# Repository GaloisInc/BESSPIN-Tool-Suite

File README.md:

```
This material is based upon work supported by the Defense Advanced
Research Project Agency (DARPA) under Contract No. HR0011-18-C-0013. 
Any opinions, findings, conclusions or recommendations expressed in
this material are those of the author(s) and do not necessarily
reflect the views of DARPA.

Distribution Statement "A" (Approved for Public Release, Distribution
Unlimited)
```

# BESSPIN-Tool-Suite #

The core tool of the BESSPIN Framework.

**Disclaimer:** *This is prototype beta software*, with support
provided to SSITH TA-1 teams.  It does not currently implement all
planned features, and contains bugs both known and unknown.  If
you encounter a problem or would like to request improvements, please
contact Galois through documented support channels.

## Table of Contents ##

- [Overview](#overview)
- [Software Requirements and Setup](#software-requirements-and-setup)
- [Usage](#usage)
- [Submodules](#submodules)
- [Developer Starter Kit](#developer-starter-kit)

___

## Overview ##

The tool performs a few different *tasks* that all revolve around the same *function*. The motivation behind the core functionality, i.e. the *function*, is to run a *program* on a target-under-test (TUT) in a robust and reproducible manner, where the TUT can be of multiple different OSes running on several different processor architectures running on multiple different backends.

In particular, the different *tasks* are called *modes*, and their different tool flows are described in detail in [modes.md](./docs/base/modes.md). The bug bounty modes have more details in [this directory](./docs/bugBounty2020/), the security evaluation mode is described in detail [here](./docs/cwesEvaluation/), and the cyberphysical demonstrator's documentation can be found [here](./docs/cyberPhys).

The different OSes are detailed in [OSes.md](./docs/base/OSes.md), while the different processors are mentioned [here](./docs/base/configuration.md), and the different backends are explained in [targets.md](./docs/base/targets.md).

---

## Software Requirements and Setup

To clone the repo and start `the nix-shell`, please use:

```bash
git clone git@github.com:GaloisInc/BESSPIN-Tool-Suite.git
cd BESSPIN-Tool-Suite
./utils/init_submodules.sh
nix-shell
```

- The `nix-shell` is the interactive shell for the Nix package manager. Please refer to [nix.md](./docs/base/nix.md) for more setup details. Please note that Nix, per version 2.3.10, is only supported on Linux (i686, x86_64, aarch64) and macOS (x86_64). [Ticket #1051 is about running the tool out-of-nix.]
- Each backend (target) has different system and setup requirements, these can be found in [targets.md](./docs/base/targets.md).
- Sudo privileges: Some parts of the tool might need sudo privileges, especially for network setup and hardware drivers access. If you do not wish to be attentive to the tool, you may just allow any sudo member to execute a group of commands without password by adding the following to the sudoers file:
```bash
    %sudo ALL=NOPASSWD: /path/to/command [flags], /path/to/another/command [flags]
```
Also, a more radical approach would be to remove all password requirements for a certain user, `${USER}`. The following can be thus added to the sudoers file:
```
${USER} ALL=(ALL) NOPASSWD:ALL
```

Alternatively, there is a docker container that has the Nix store populated, and is ready to go. The resources needed to build the docker container are currently in [the docker directory](https://github.com/GaloisInc/BESSPIN-Environment/tree/master/docker/). The docker image is `galoisinc/besspin:tool-suite`, and requires Galois artifactory access to fetch. The recommended command to start the image is:
```bash
    sudo docker run -it --privileged=true --network host -v /path/to/BESSPIN-Tool-Suite:/home/besspinuser/BESSPIN-Tool-Suite galoisinc/besspin:tool-suite
```

---

## Usage ##

To run the tool, use the following:
```
usage: besspin.py [-h] [-c CONFIGFILE | -cjson CONFIGFILESERIALIZED]
               [-w WORKINGDIRECTORY] [-l LOGFILE] [-d]
               [-ep {devHost,ciOnPrem,ciAWS,awsProd,awsDev}] [-job JOBID]

BESSPIN (Balancing Evaluation of System Security Properties with Industrial Needs)

optional arguments:
  -h, --help            show this help message and exit
  -c CONFIGFILE, --configFile CONFIGFILE
                        Overwrites the default config file: ./config.ini
  -cjson CONFIGFILESERIALIZED, --configFileSerialized CONFIGFILESERIALIZED
                        Overwrites and augments the default production
                        settings
  -w WORKINGDIRECTORY, --workingDirectory WORKINGDIRECTORY
                        Overwrites the default working directory: ./workDir/
  -l LOGFILE, --logFile LOGFILE
                        Overwrites the default logFile: ./${workDir}/besspin.log
  -d, --debug           Enable debugging mode.
  -ep {devHost,ciOnPrem,ciAWS,awsProd,awsDev}, --entrypoint {devHost,ciOnPrem,ciAWS,awsProd,awsDev}
                        The entrypoint
  -job JOBID, --jobId JOBID
                        The job ID in production mode.
```

Configuration is explained in detail in [configuration.md](./docs/base/configuration.md). Although `-cjson` is an alternative option, it is strongly recommended to use an INI file as the document describes. The serialized option is specific to the production mode in bug bounty, and is intended to be used automatically by a cloud hook script on a host instantiated by the bug bounty website; more details can be found in [the bug bounty documentation](./docs/bugBounty2020/).

If the tool is executed manually, there is no need to provide an entrypoint (will be assigned `devHost` by default), or a job ID. These are for when the tool is executed in batch test mode and CI.

The debug mode will dramatically increase the size of the log file (`./${workDir}/besspin.log` by default), so please use it only if needed.

---

## Submodules ##

The tool has the following submodules:
- [BESSPIN-Environment](./BESSPIN-Environment): The Nix shell source codes for the required packages and binaries. More details about Nix are in [nix.md](./docs/base/nix.md).
- [BESSPIN-Voter-Registration](./BESSPIN-Voter-Registration): As detailed [here](./docs/bugBounty2020/), a voting registration system was one of the applications in the attack surface for the Unix targets of the bug bounty. This submodule has documentation, build instructions, source codes, design files, etc.
- [BESSPIN-LFS](./BESSPIN-LFS): This is the Git LFS repo that contains many resources the tool needs for certain configurations, like OS binaries, FPGA bitstreams, AWS AFI IDs, application pre-built binaries, etc.
- [FreeRTOS](./FreeRTOS): The Galois fork of the classic FreeRTOS repo. This is used for building the FreeRTOS binaries since each CWE test and each application needs to be cross-built alongside the FreeRTOS kernel in a single binary. 

---

## Developer Starter Kit ##

- The target classes structure is briefly explained in [targets.md](./docs/base/targets.md). This should be the starting point to add a new OS or a new backend to the tool.
- There are many functions that are used throughout the tool and can help with integration. These functions are defined inside `besspin/base/utils/misc.py`. It would be useful to look at this file prior to any development work on this codebase. Especially `printAndLog`, `warnAndLog`, `errorAndLog`, `logAndExit`, `getSetting`, `ftOpenFile`, `make`.
- To add a configuration option, you have to update the json dictionary in `besspin/base/utils/configData.json`.
- To add/change a system setting, you have to update the json dictionary in `besspin/base/utils/setupEnv.json`.
- The directories structure is:
  - `apps`: Bug bounty specific.
  - `base`: The core functionality (ex. target)
  - `cwesEvaluation`: Security evaluation specific.
  - `cyberPhys`: Cyberphysical demonstrator functions.
  - `target`: The backend classes in addition to the start/launch/end functions.
- [modes.md](./docs/base/modes) has some low-level details about how the tool works in different modes. It's definitely a recommended read before development.

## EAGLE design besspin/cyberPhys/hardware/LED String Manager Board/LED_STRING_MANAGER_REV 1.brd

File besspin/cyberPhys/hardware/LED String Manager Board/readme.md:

# Introduction
The LED String Manager Board is a Fadecandy-based LED string manager solution which provides a tidy, robust power and data solution for strings of individually addressable 12 volt LEDs commonly referred to as Neopixels.

Up to eight strings of 63 LEDs can be driven using this board. A Fadecandy board and a USB relay are necessary.

Schematic and Board were created using Eagle 9.6.2 Premium. The following design artifacts are included in this repository:
- Schematic and Board Layout files
- Bill of Materials
- Gerber files

# 12 Volt Power
The board is powered with 12 volts through common 0.250 inch spade connectors. Wiring which can accommodate up to 7.5 amperes is recommended as well as a 7.5 ampere automotive standard blade fuse.

# LED String Interface
Each LED string _requires_ three circuits:
- 12 volts (Blue)
- Data (Red)
- Ground (Black)

There is a second, backup data line which is not used.

Each LED string is terminated in a JST P/N SMP-04V-BC connector as shown in the following image.

Any 100 mil spaced male header may be used for LED string connections at CN2 through CN9. The boards in the CyberPhysical demonstrator use Molex P/N 0901361204, which is a shrouded header with a key clip. Each four circuit harness used in the CyberPhysical demonstrator consists of the following:

- 1 x Molex P/N 0901560144 (housing)
- 4 x Molex P/N 0901192109 (crimp contacts, requires Molex Crimp Tool P/N 0638258100)
- Varied length of 4-circuit LED extension wire
- 1 x JST P/N SMR-04V-B (housing)
- 4 x JST P/N SYM-001T-P0.6(N) (crimp contacts)

Pin #1 of the Molex connector is 12 volts (Blue).

# Example Installation
The following image shows an LED String Manager Board installed in the CyberPhysical demonstrator with variable length LED string interface harnesses.

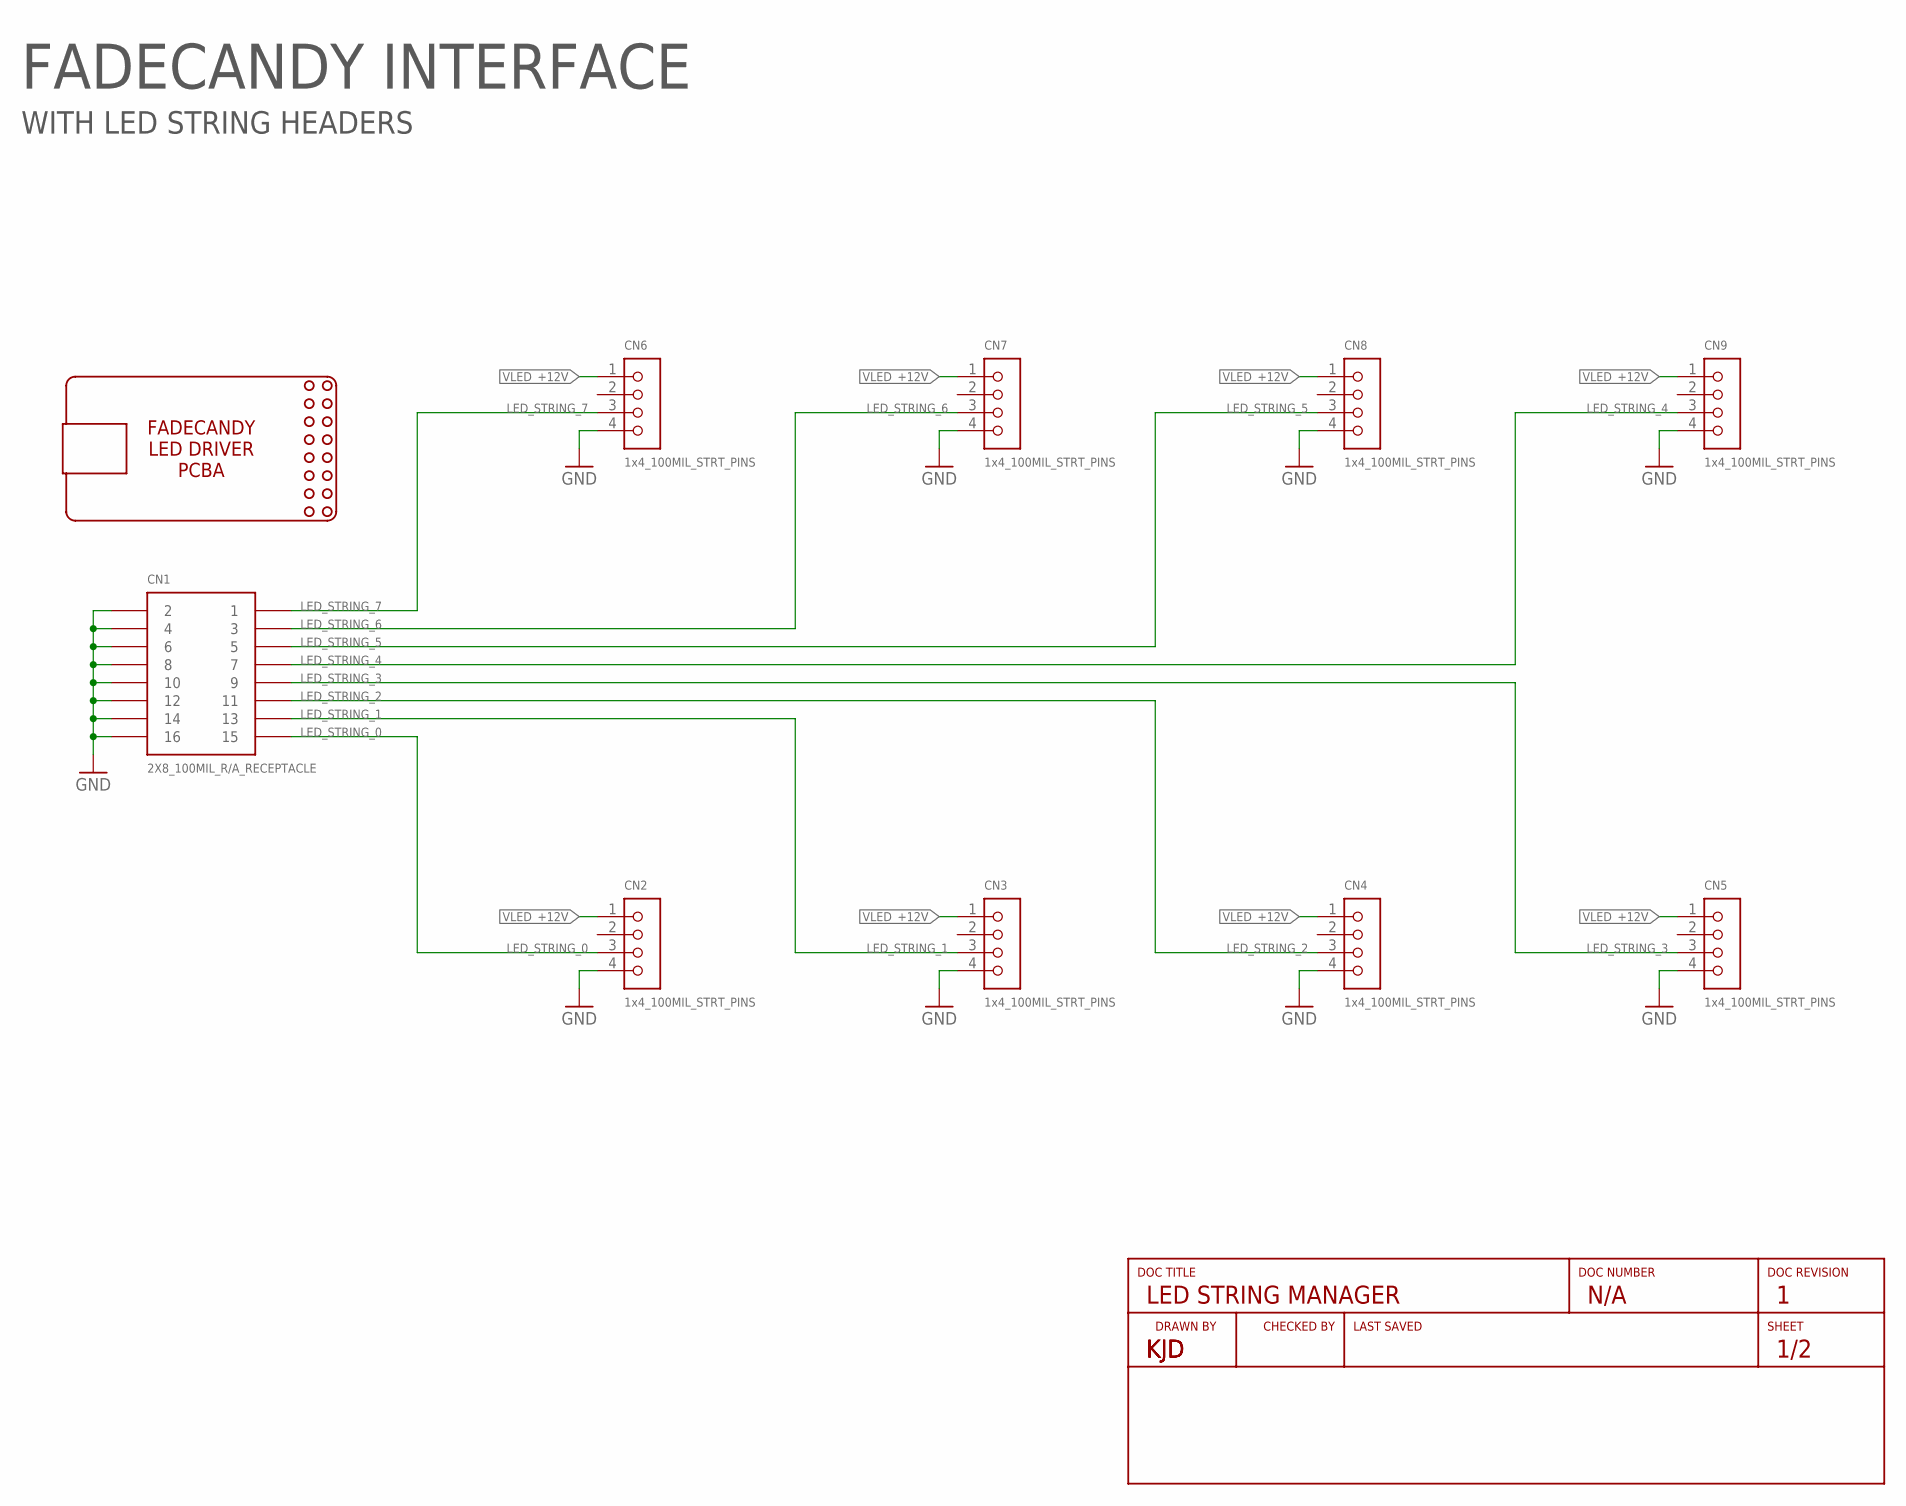
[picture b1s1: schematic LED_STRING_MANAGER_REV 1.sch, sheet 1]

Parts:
CN1: 2X8_100MIL_R/A_RECEPTACLE; 2X8_100MIL_R/A; MPN PPPC082LJBN-RC
CN2, CN3, CN4, CN5, CN6, CN7, CN8, CN9: 1x4_100MIL_STRT_PINS; 1X4_0901361204; MPN 0901361204
U$3: FADECANDY_PCB_FOOTPRINT

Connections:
GND: CN1.2, CN1.4, CN1.6, CN1.8, CN1.10, CN1.12, CN1.14, CN1.16, CN2.4, CN3.4, CN4.4, CN5.4, CN6.4, CN7.4, CN8.4, CN9.4; also elsewhere on the board
LED_STRING_0: CN1.15, CN2.3
LED_STRING_1: CN1.13, CN3.3
LED_STRING_2: CN1.11, CN4.3
LED_STRING_3: CN1.9, CN5.3
LED_STRING_4: CN1.7, CN9.3
LED_STRING_5: CN1.5, CN8.3
LED_STRING_6: CN1.3, CN7.3
LED_STRING_7: CN1.1, CN6.3
VLED_+12V: CN2.1, CN3.1, CN4.1, CN5.1, CN6.1, CN7.1, CN8.1, CN9.1; also elsewhere on the board

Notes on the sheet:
FADECANDY INTERFACE
WITH LED STRING HEADERS
KJD

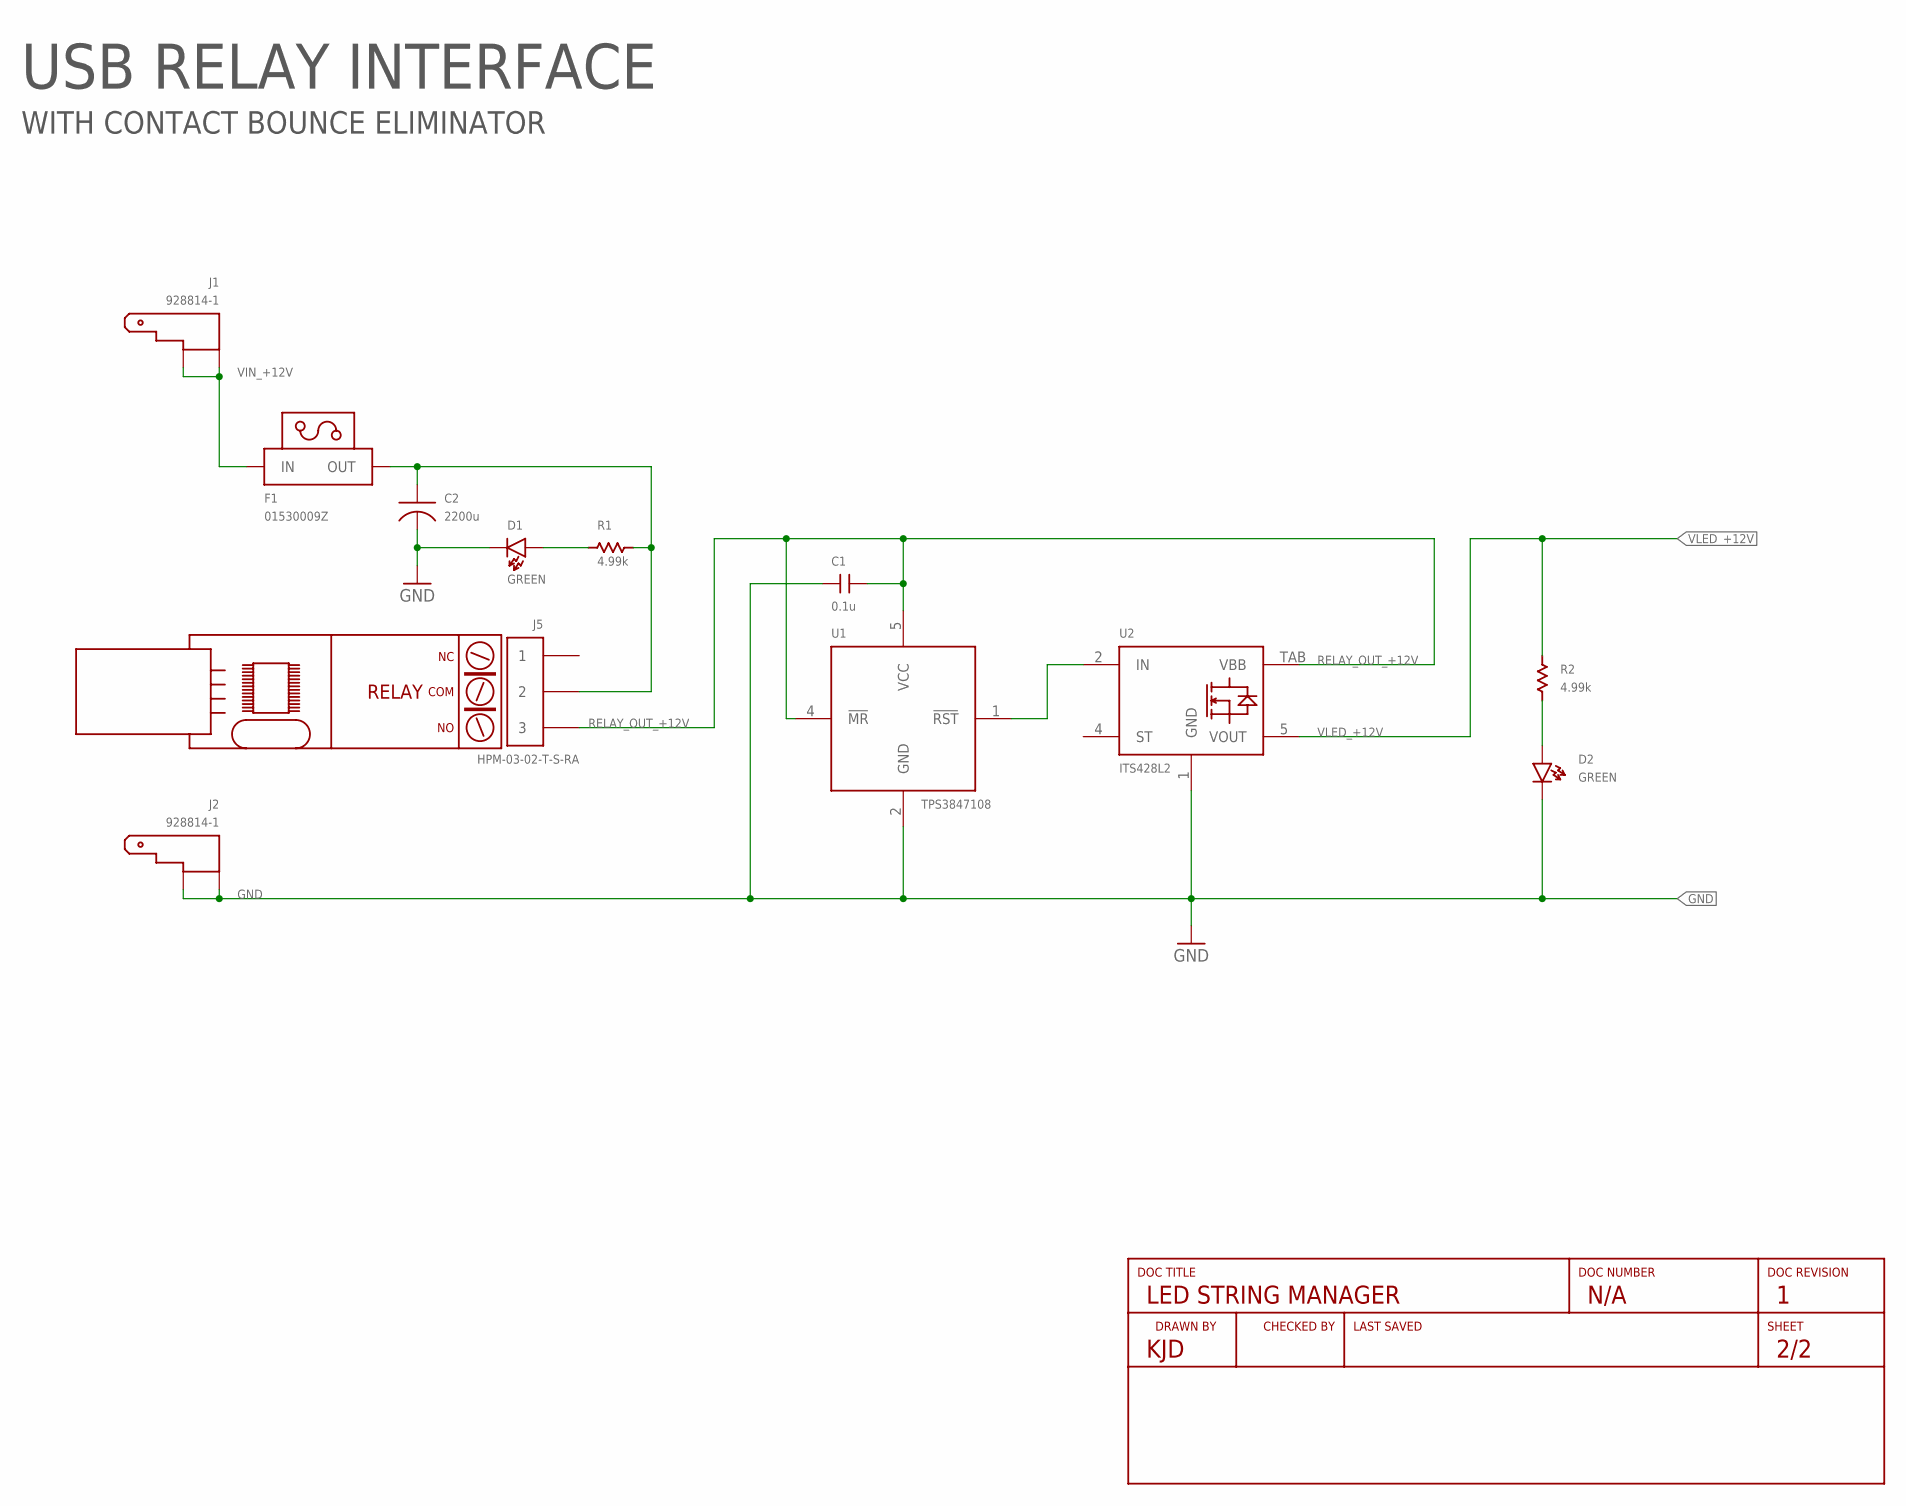
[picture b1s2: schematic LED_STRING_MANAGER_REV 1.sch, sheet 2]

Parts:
C1: 0.1u; EIA0603; MPN CL10B104KB8NNNC
C2: 2200u; PANASONIC_HD_12.5MM; MPN EEU-HD1E222
D1, D2: GREEN; EIA0603_LED; MPN LG Q396-PS-35
F1: 01530009Z; LITTELFUSE_MINI_BLADE_HOLDER_01530009; MPN 01530009Z
J1, J2: 928814-1; FASTON_MALE_SERIES_250_THRU_R/A; MPN 928814-1
J5: HPM-03-02-T-S-RA; HPM_1X3_R/A; MPN HPM-03-02-T-S-RA
R1, R2: 4.99k; EIA0603; MPN ERJ-3EKF4991V
U1: TPS3847108; SOT23-5; MPN TPS3847108DBVR
U2: ITS428L2; PG-TO252-5-11; MPN ITS428L2ATMA1
U$4: USB_RELAY_PCB_FOOTPRINT

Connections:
FUSED_+12V: C2.C+, F1.2 (OUT), J5.2, R1.P$2
GND: C1.P$1, C2.C-, D1.C, D2.C, J2.1, J2.2, U1.2 (GND), U2.1 (GND); also elsewhere on the board
unnamed: D2.A, R2.P$1
unnamed: D1.A, R1.P$1
unnamed: U1.1 (!RST), U2.2 (IN)
RELAY_OUT_+12V: C1.P$2, J5.3, U1.4 (!MR), U1.5 (VCC), U2.TAB (VBB)
VIN_+12V: F1.1 (IN), J1.1, J1.2
VLED_+12V: R2.P$2, U2.5 (VOUT); also elsewhere on the board

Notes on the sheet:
USB RELAY INTERFACE
WITH CONTACT BOUNCE ELIMINATOR

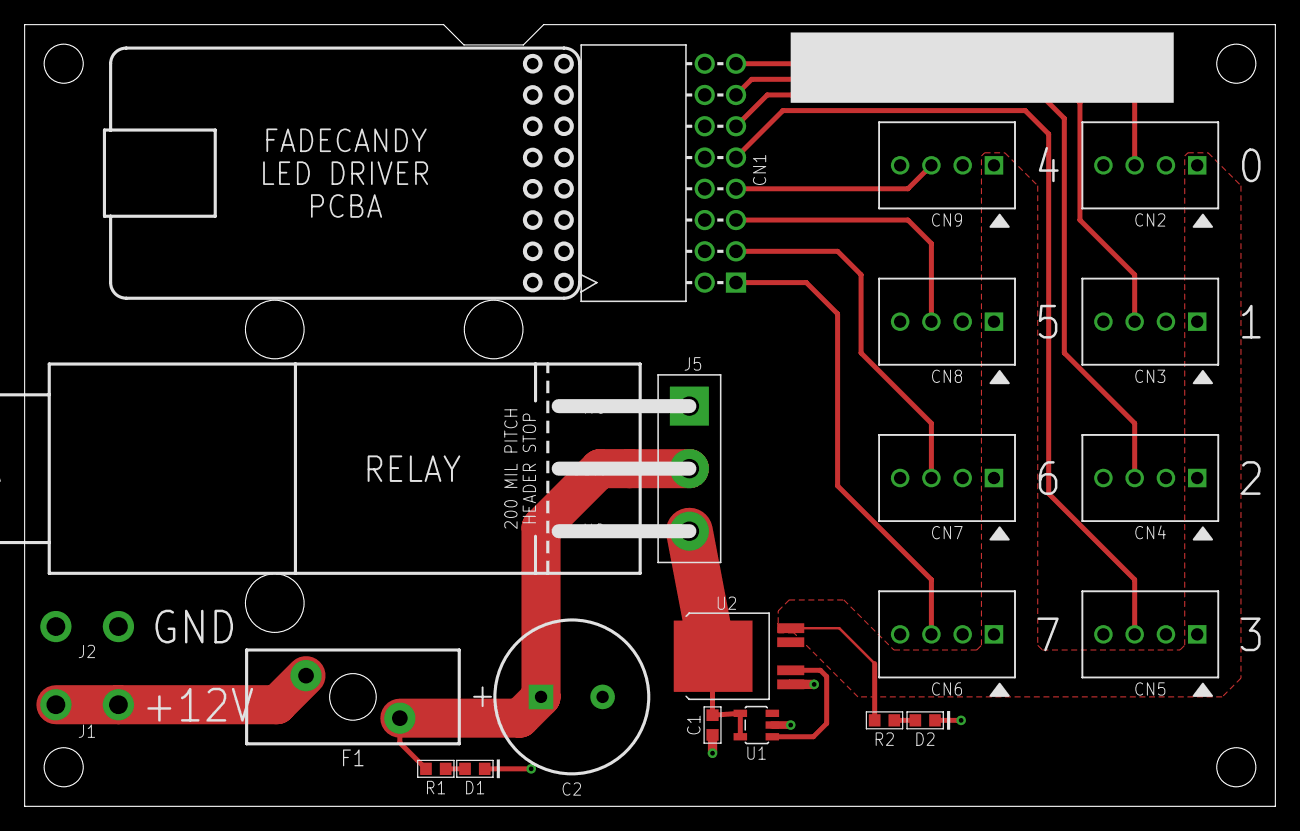
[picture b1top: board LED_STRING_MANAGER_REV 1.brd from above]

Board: 2 copper layers, 101.6 x 63.5 mm, 23 parts (0 on the bottom side), 16 nets.

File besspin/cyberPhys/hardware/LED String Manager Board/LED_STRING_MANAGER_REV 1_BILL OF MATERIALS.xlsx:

Qty | Value | Device | Package | Parts | Description | MPN | PACKAGE.1 | Column1
1 | 0.1u | C_SMDC0603 | EIA0603 | C1 |  | CL10B104KB8NNNC | 603
1 | 01530009Z | FUSE_HOLDER_AUTOMOTIVE_MINI_BLADE | LITTELFUSE_MINI_BLADE_HOLDER_01530009 | F1 |  | 01530009Z
8 | 1x4_100MIL_STRT_PINS | MOLEX_CGRID_III_0901361204 | 1X4_0901361204 | CN2, CN3, CN4, CN5, CN6, CN7, CN8, CN9 |  | 0901361204
1 | 2200u | C_POLARIZED_DIA_12.5MM_LEADS_5MM | PANASONIC_HD_12.5MM | C2 |  | EEU-HD1E222
1 | 2X8_100MIL_R/A_RECEPTACLE | 2X8_RIGHT_ANGLE | 2X8_100MIL_R/A | CN1 |  | PPPC082LJBN-RC
2 | 4.99k | R_SMDR0603 | EIA0603 | R1, R2 |  | ERJ-3EKF4991V | 603
2 | 928814-1 | FASTON_PCB_THRU_R/A | FASTON_MALE_SERIES_250_THRU_R/A | J1, J2 |  | 928814-1
1 | FADECANDY_PCB_FOOTPRINT | FADECANDY_PCB_FOOTPRINT | FADECANDY_PCB_FOOTPRINT | U$3
2 | GREEN | LED_SMD | EIA0603_LED | D1, D2 |  | LG Q396-PS-35
1 | HPM-03-02-T-S-RA | HPM_1X3_R/A | HPM_1X3_R/A | J5 |  | HPM-03-02-T-S-RA
1 | ITS428L2 | ITS428L2 | PG-TO252-5-11 | U2 |  | ITS428L2ATMA1
1 | TPS3847108 | TPS3847 | SOT23-5 | U1 |  | TPS3847108DBVR
1 | USB_RELAY_PCB_FOOTPRINT | USB_RELAY_PCB_FOOTPRINT | USB_RELAY_PCB_FOOTPRINT | U$4

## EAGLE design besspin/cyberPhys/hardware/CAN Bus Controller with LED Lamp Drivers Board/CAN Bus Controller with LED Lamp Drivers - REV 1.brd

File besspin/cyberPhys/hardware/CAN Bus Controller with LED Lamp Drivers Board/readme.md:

# Introduction
The CAN Bus Controller with LED Lamp Drivers Board (REV 1) is a Teensy 3.6-based solution with a variety of embedded circuitry and system interfaces including:
- UART
- I2C x 3
- CAN bus
- Analog sensing
- Digital I/O
- PWM outputs

Schematic and Board were created using Eagle 9.6.2 Premium. The following design artifacts are included in this repository:
- Schematic and Board Layout files
- Bill of Materials
- Gerber files

# 12 Volt Power Input Option
There is a 12 volt power input option in CN2. Pin #1 is +12 volts. Pin #2 is ground. Read the following sections for more information on how it works. Do not exceed 30 volts on this input connector.

## Teensy 3.6 Power
The Teensy 3.6 can be powered via the USB port _or_ the 12 volt input (CN2). __If using the 12 volt input and the Teensy 3.6 is connected to USB, Jumper J1 should be open circuit.__

## Downstream Device Power
This board is typically connected in some fashion to a downstream automotive device such as an instrument cluster or a gear shifter assembly. When this is the case, wiring can be kept tidy by running power through this board from CN2 to CN1 and/or CN4. __If using the 12 volt input and the Teensy 3.6 is connected to USB, Jumper J1 should be open circuit.__

# CAN Bus
There is a Texas Instruments automotive grade TCAN332 transceiver (U2) with on-board termination (R3). It runs from +3.3V, which makes it a good match for the Teensy 3.6. More information is here: https://www.ti.com/product/TCAN332. Note that in this design, the CAN bus is interfaced to the alternative pins on the Teensy 3.6.

# LED Lamp Drivers
There are four LED lamp driver interfaces across CN9 and CN10 labeled LED1, LED2, LED3, and LED4. Practically speaking, each one of these outputs is merely 12 volts switched on or off to the LED's anode through a smart high side switch (https://www.infineon.com/cms/en/product/power/smart-low-side-high-side-switches/high-side-switches/classic-profet-12v-automotive-smart-high-side-switch/bts5014sda/). Given this, these outputs can also be used to power a 12 volt downstream device. _Do not exceed a 1 amp per LED channel._

## LED Lamp Driver Alternate Control
The LED Lamp Drivers can be controlled through CN8. A positive signal applied to CTRL_LED_BULB_# will activate the associated smart switch. _In order to use the alternate control input, R12, R13, R14, and R15 must be removed from the printed circuit board assembly._

If using a VCU118-based GPIO for this control interface, MOSFETs Q2, Q3, Q4, and Q5 should be replaced with __Infineon BSR802NL6327HTSA1__ to ensure compatibility with its positive output signal.

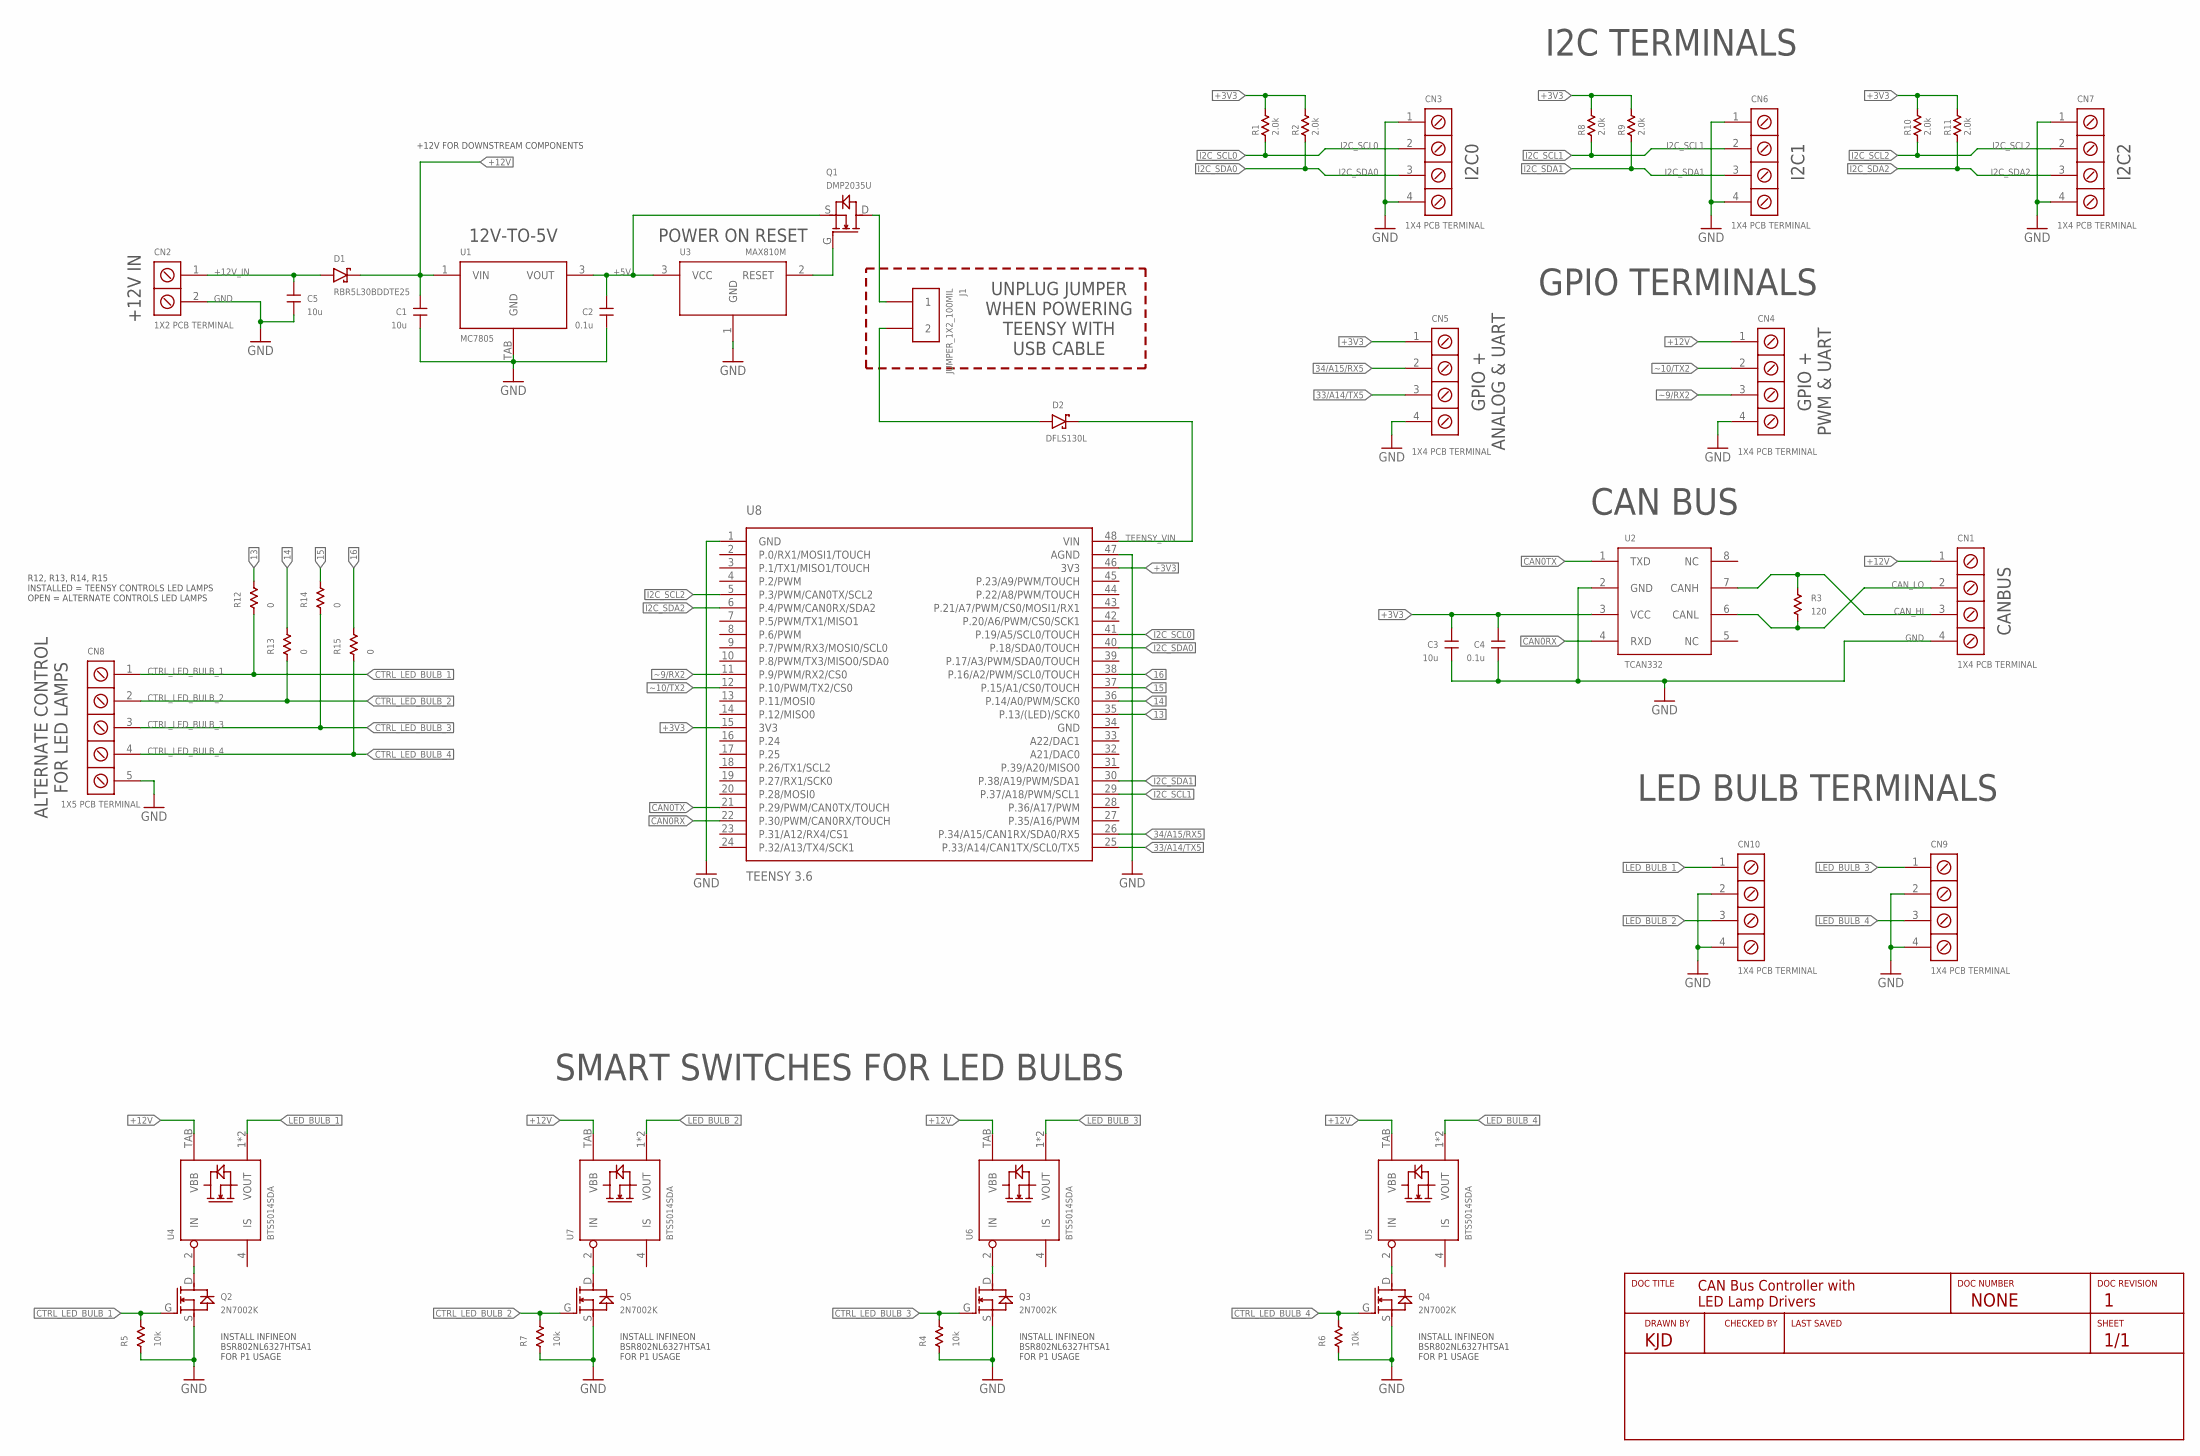
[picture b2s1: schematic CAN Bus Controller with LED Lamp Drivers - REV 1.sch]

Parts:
C1, C3, C5: 10u; EIA1206; MPN CL31A106KBHNNNE
C2, C4: 0.1u; EIA0603; MPN CL10B104KA8NNNC
CN1, CN3, CN4, CN5, CN6, CN7, CN9, CN10: 1X4 PCB TERMINAL; PCB_TERM_3.5MM_PITCH_1X4; MPN 1984633
CN2: 1X2 PCB TERMINAL; PCB_TERM_3.5MM_PITCH_1X2; MPN 1984617
CN8: 1X5 PCB TERMINAL; PCB_TERM_3.5MM_PITCH_1X5; MPN 1984646
D1: RBR5L30BDDTE25; SMA; MPN RBR5L30BDDTE25
D2: DFLS130L; POWERDI_123; MPN DFLS130L-7
J1: JUMPER_1X2_100MIL; 1X2_100MIL_THRU; MPN QPC02SXGN-RC
Q1: DMP2035U; SOT-23-3; MPN DMP2035U-7
Q2, Q3, Q4, Q5: 2N7002K; SOT-23-3; MPN 2N7002K-7
R1, R2, R8, R9, R10, R11: 2.0k; EIA0603; MPN ERJ-3EKF2001V
R3: 120; EIA1210; MPN AC1210FR-07120RL
R4, R5, R6, R7: 10k; EIA0603; MPN ERJ-3EKF1002V
R12, R13, R14, R15: 0; EIA0603; MPN ERJ-3GEY0R00V
U1: MC7805; DPAK-3; MPN MC7805CDTRKG
U2: TCAN332; SOIC-8; MPN TCAN332DR
U3: MAX810M; SOT23-3; MPN MAX810MTRG
U4, U5, U6, U7: BTS5014SDA; PG-TO252-5-11; MPN BTS5014SDAAUMA1
U8: TEENSY 3.6; TEENSY3.6

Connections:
13: R12.P$2, U8.35 (P.13/(LED)/SCK0)
14: R13.P$2, U8.36 (P.14/A0/PWM/SCK0)
15: R14.P$2, U8.37 (P.15/A1/CS0/TOUCH)
16: R15.P$2, U8.38 (P.16/A2/PWM/SCL0/TOUCH)
33/A14/TX5: CN5.3, U8.25 (P.33/A14/CAN1TX/SCL0/TX5)
34/A15/RX5: CN5.2, U8.26 (P.34/A15/CAN1RX/SDA0/RX5)
+3V3: C3.P$2, C4.P$2, CN5.1, R1.P$2, R2.P$2, R8.P$2, R9.P$2, R10.P$2, R11.P$2, U2.3 (VCC), U8.15 (3V3), U8.46 (3V3)
+5V: C2.P$2, Q1.S, U1.3 (VOUT), U3.3 (VCC)
+12V: C1.P$2, CN1.1, CN4.1, D1.C, U1.1 (VIN), U4.TAB (VBB), U5.TAB (VBB), U6.TAB (VBB), U7.TAB (VBB)
+12V_IN: C5.P$2, CN2.1, D1.A
CAN0RX: U2.4 (RXD), U8.22 (P.30/PWM/CAN0RX/TOUCH)
CAN0TX: U2.1 (TXD), U8.21 (P.29/PWM/CAN0TX/TOUCH)
CAN_HI: CN1.3, R3.P$2, U2.7 (CANH)
CAN_LO: CN1.2, R3.P$1, U2.6 (CANL)
CTRL_LED_BULB_1: CN8.1, Q2.G, R5.P$2, R12.P$1
CTRL_LED_BULB_2: CN8.2, Q5.G, R7.P$2, R13.P$1
CTRL_LED_BULB_3: CN8.3, Q3.G, R4.P$2, R14.P$1
CTRL_LED_BULB_4: CN8.4, Q4.G, R6.P$2, R15.P$1
GND: C1.P$1, C2.P$1, C3.P$1, C4.P$1, C5.P$1, CN1.4, CN2.2, CN3.1, CN3.4, CN4.4, CN5.4, CN6.1, CN6.4, CN7.1, CN7.4, CN8.5, CN9.2, CN9.4, CN10.2, CN10.4, Q2.S, Q3.S, Q4.S, Q5.S, R4.P$1, R5.P$1, R6.P$1, R7.P$1, U1.TAB (GND), U2.2 (GND), U3.1 (GND), U8.1 (GND), U8.47 (AGND)
I2C_SCL0: CN3.2, R1.P$1, U8.41 (P.19/A5/SCL0/TOUCH)
I2C_SCL1: CN6.2, R8.P$1, U8.29 (P.37/A18/PWM/SCL1)
I2C_SCL2: CN7.2, R10.P$1, U8.5 (P.3/PWM/CAN0TX/SCL2)
I2C_SDA0: CN3.3, R2.P$1, U8.40 (P.18/SDA0/TOUCH)
I2C_SDA1: CN6.3, R9.P$1, U8.30 (P.38/A19/PWM/SDA1)
I2C_SDA2: CN7.3, R11.P$1, U8.6 (P.4/PWM/CAN0RX/SDA2)
LED_BULB_1: CN10.1, U4.1 (VOUT), U4.5 (VOUT)
LED_BULB_2: CN10.3, U7.1 (VOUT), U7.5 (VOUT)
LED_BULB_3: CN9.1, U6.1 (VOUT), U6.5 (VOUT)
LED_BULB_4: CN9.3, U5.1 (VOUT), U5.5 (VOUT)
unnamed: J1.1, Q1.D
unnamed: D2.A, J1.2
unnamed: Q2.D, U4.2 (IN)
unnamed: Q4.D, U5.2 (IN)
unnamed: Q5.D, U7.2 (IN)
unnamed: Q3.D, U6.2 (IN)
unnamed: Q1.G, U3.2 (RESET)
TEENSY_VIN: D2.C, U8.48 (VIN)
~9/RX2: CN4.3, U8.11 (P.9/PWM/RX2/CS0)
~10/TX2: CN4.2, U8.12 (P.10/PWM/TX2/CS0)

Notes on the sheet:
CANBUS
I2C0
12V-TO-5V
POWER ON RESET
UNPLUG JUMPER WHEN POWERING TEENSY WITH USB CABLE
GPIO + PWM & UART
GPIO + ANALOG & UART
CAN Bus Controller with LED Lamp Drivers
KJD
NONE
INSTALL INFINEON BSR802NL6327HTSA1 FOR P1 USAGE
I2C1
I2C2
I2C TERMINALS
GPIO TERMINALS
CAN BUS
+12V IN
+12V FOR DOWNSTREAM COMPONENTS
SMART SWITCHES FOR LED BULBS
ALTERNATE CONTROL FOR LED LAMPS
LED BULB TERMINALS
R12, R13, R14, R15 INSTALLED = TEENSY CONTROLS LED LAMPS OPEN = ALTERNATE CONTROLS LED LAMPS

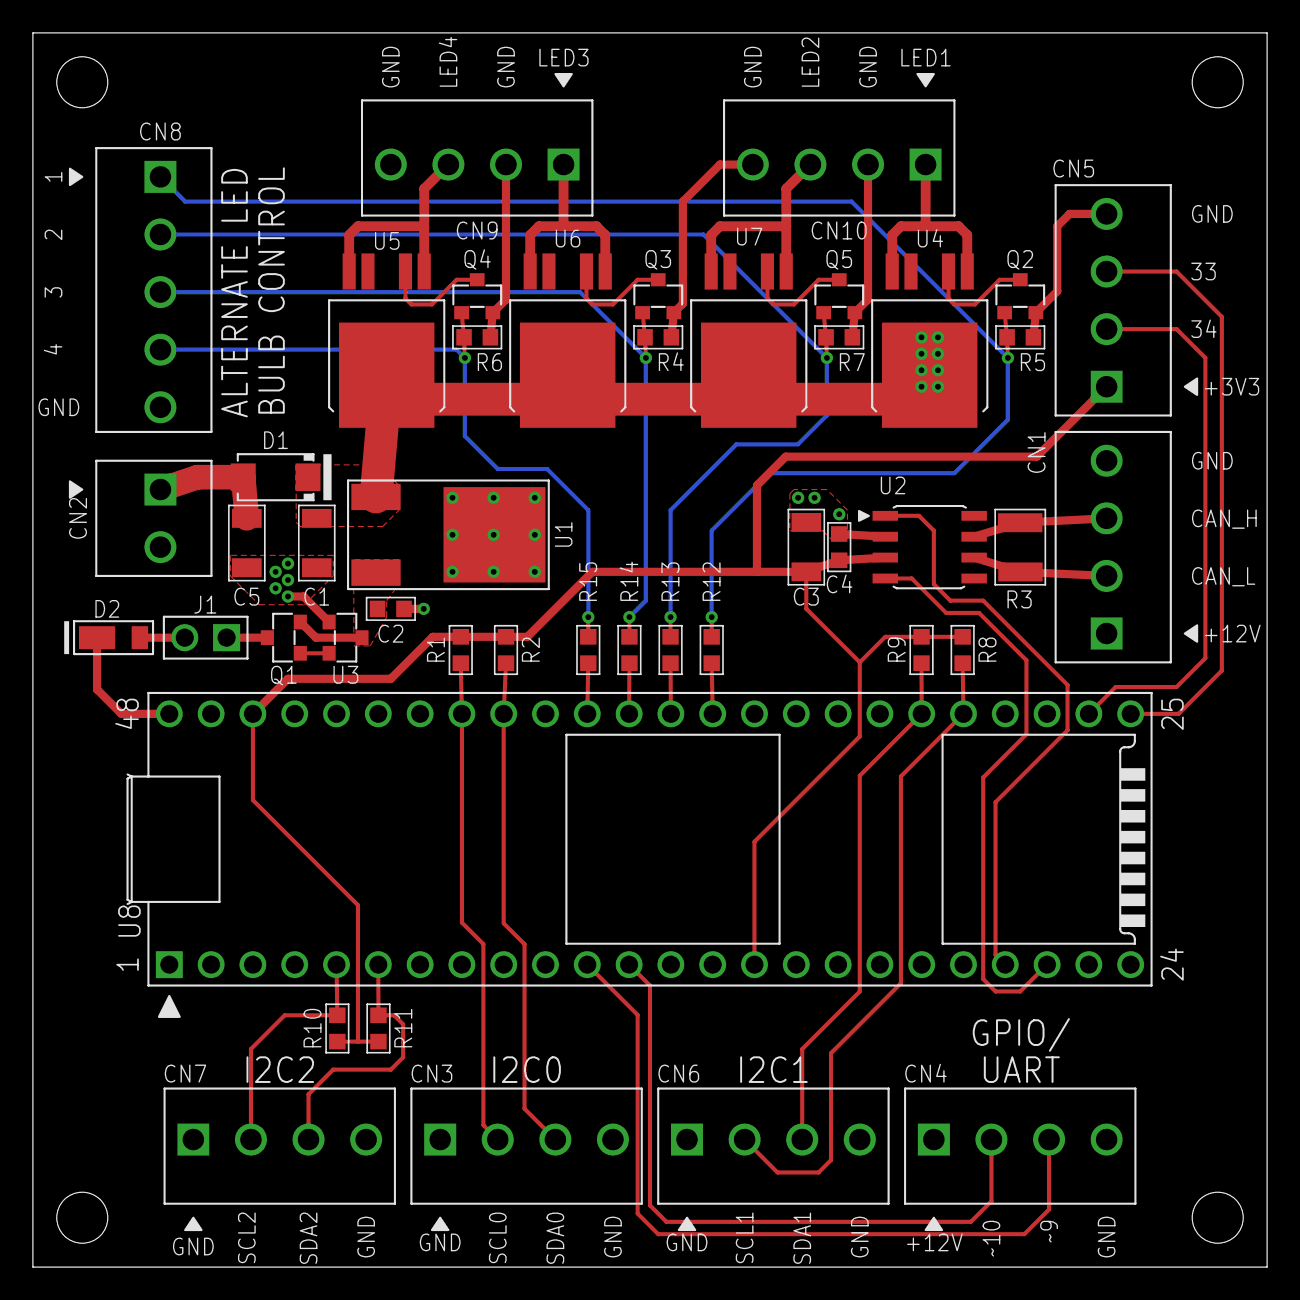
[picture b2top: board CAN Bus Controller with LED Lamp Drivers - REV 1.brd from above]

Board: 4 copper layers, 75.0 x 75.0 mm, 46 parts (0 on the bottom side), 39 nets.

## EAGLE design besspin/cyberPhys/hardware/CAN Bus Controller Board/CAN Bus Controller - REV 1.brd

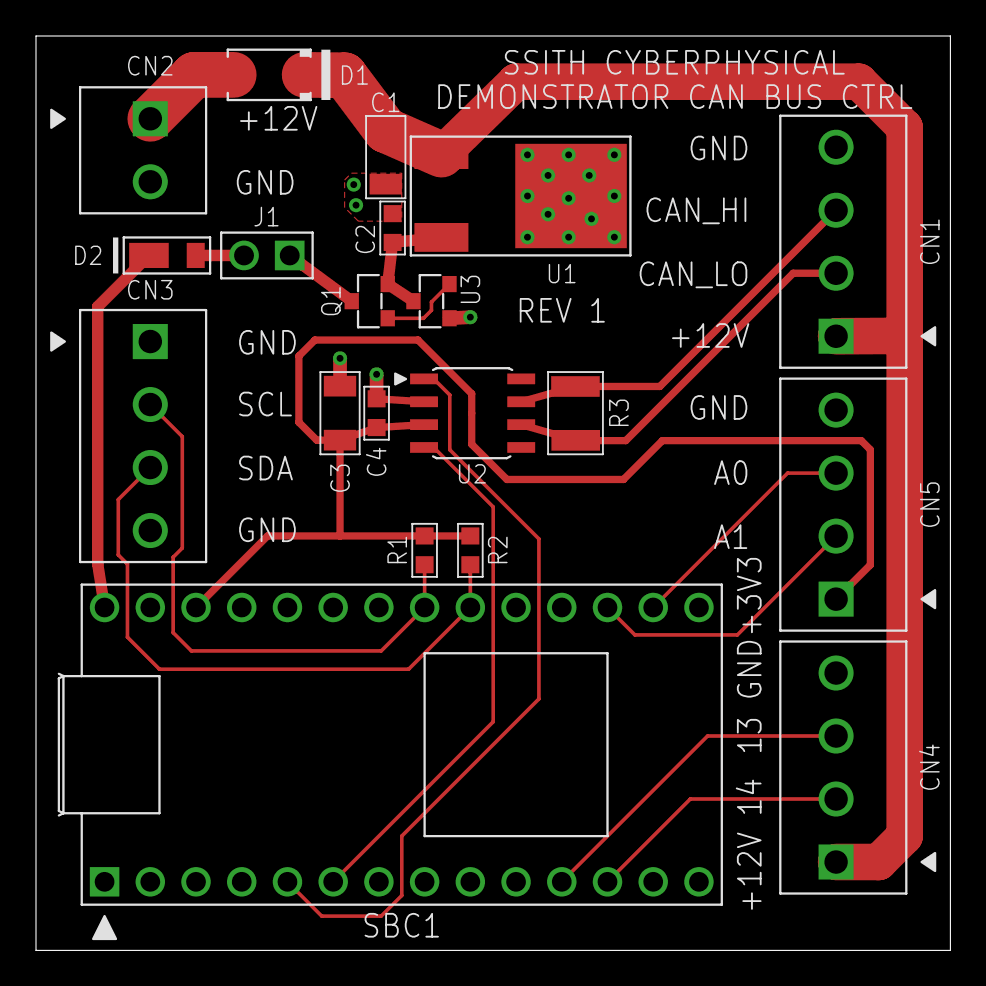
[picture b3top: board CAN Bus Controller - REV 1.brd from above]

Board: 2 copper layers, 50.8 x 50.8 mm, 20 parts (0 on the bottom side), 19 nets.

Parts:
C1, C3: 10u; EIA1206
C2, C4: 0.1u; EIA0603
CN1, CN3, CN4, CN5: 1X4 PCB TERMINAL; PCB_TERM_3.5MM_PITCH_1X4
CN2: 1X2 PCB TERMINAL; PCB_TERM_3.5MM_PITCH_1X2
D1: RBR5L30BDDTE25; SMA
D2: DFLS130L; POWERDI_123
J1: JUMPER_1X2_100MIL; 1X2_100MIL_THRU
Q1: DMP2035U; SOT-23-3
R1, R2: 4.7k; EIA0603
R3: 120; EIA1210
SBC1: TEENSY 3.2; TEENSY3.2
U1: MC7805; DPAK-3
U2: TCAN332; SOIC-8
U3: MAX810M; SOT23-3

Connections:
12V: C1.P$2, CN1.1, CN4.1, D1.C, U1.1
12V_IN: CN2.1, D1.A
+3V3: C3.P$2, C4.P$2, CN5.1, R1.P$2, R2.P$2, SBC1.26, U2.3
+5V: C2.P$2, Q1.S, U1.3, U3.3
A0: CN5.3, SBC1.16
A1: CN5.2, SBC1.17
CAN0RX: SBC1.6, U2.4
CAN0TX: SBC1.5, U2.1
CAN_HI: CN1.3, R3.P$2, U2.7
CAN_LO: CN1.2, R3.P$1, U2.6
GND: C1.P$1, C2.P$1, C3.P$1, C4.P$1, CN1.4, CN2.2, CN3.1, CN3.4, CN4.4, CN5.4, SBC1.1, SBC1.27, U1.TAB, U2.2, U3.1
I2C_SCL: CN3.2, R1.P$1, SBC1.21
I2C_SDA: CN3.3, R2.P$1, SBC1.20
unnamed: J1.1, Q1.D
unnamed: D2.A, J1.2
unnamed: Q1.G, U3.2
TEENSY_VIN: D2.C, SBC1.28
~9: CN4.3, SBC1.11
~10: CN4.2, SBC1.12
